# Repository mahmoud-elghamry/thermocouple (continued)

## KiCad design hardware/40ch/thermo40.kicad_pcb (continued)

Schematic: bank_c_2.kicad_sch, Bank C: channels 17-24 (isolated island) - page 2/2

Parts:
C361, C371, C381: 10n C0G; C_0805_2012Metric; MPN GRM2195C1H103JA01D; LCSC C97905
C362, C363, C372, C373, C382, C383: 1n C0G; C_0805_2012Metric; MPN CL21C102JBCNNNC; LCSC C1791
C389, C390, C391, C392, C393, C394, C396, C398, C399: 100n; C_0805_2012Metric; MPN CC0805KRX7R9BB104; LCSC C49678
C395, C397: 1u; C_0805_2012Metric; MPN CL21B105KBFNNNE; LCSC C28323
D361, D362, D371, D372, D381, D382: BAV199; SOT-23; MPN BAV199,215; LCSC C40919
R361, R362, R371, R372, R381, R382: 2.2k; R_0805_2012Metric; MPN 0805W8F2201T5E; LCSC C17520
R363, R364, R373, R374, R383, R384: 1k; R_0805_2012Metric; MPN 0805W8F1001T5E; LCSC C17513
R365, R375, R385: 20M 1%; R_1206_3216Metric; MPN FRG1206F2005TS; LCSC C3000606
U301: AD7124-8BCPZ; LFCSP-32-1EP_5x5mm_P0.5mm_EP3.6x3.6mm; MPN AD7124-8BCPZ; LCSC C97314
U302, U303: TMP126DCKR; SOT-363_SC-70-6; MPN TMP126DCKR; LCSC C5219998

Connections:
+3V3_ISO: C390.1, C394.1, C395.1, C396.1, C397.1, C399.1, D361.2 (K), D362.2 (K), D371.2 (K), D372.2 (K), D381.2 (K), D382.2 (K), U301.2 (IOVDD), U301.26 (AVDD), U301.27 (SYNC), U302.6 (VDD), U303.6 (VDD); also elsewhere on the board
/BANK_C_2/REFOUT_C: C391.1, U301.22 (REFOUT)
/BANK_C_2/REGCAPA_C: C392.1, U301.24 (REGCAPA)
/BANK_C_2/REGCAPD_C: C393.1, U301.1 (REGCAPD)
/BANK_C_2/TC22_NA: C361.2, C363.1, R364.2, U301.17 (AIN11)
/BANK_C_2/TC22_NC: D362.3 (common), R362.2, R364.1
/BANK_C_2/TC22_PA: C361.1, C362.1, R363.2, U301.16 (AIN10)
/BANK_C_2/TC22_PC: D361.3 (common), R361.2, R363.1
/BANK_C_2/TC23_NA: C371.2, C373.1, R374.2, U301.19 (AIN13)
/BANK_C_2/TC23_NC: D372.3 (common), R372.2, R374.1
/BANK_C_2/TC23_PA: C371.1, C372.1, R373.2, U301.18 (AIN12)
/BANK_C_2/TC23_PC: D371.3 (common), R371.2, R373.1
/BANK_C_2/TC24_NA: C381.2, C383.1, R384.2, U301.21 (AIN15)
/BANK_C_2/TC24_NC: D382.3 (common), R382.2, R384.1
/BANK_C_2/TC24_PA: C381.1, C382.1, R383.2, U301.20 (AIN14)
/BANK_C_2/TC24_PC: D381.3 (common), R381.2, R383.1
CS_ADC3_ISO: U301.32 (~CS); also elsewhere on the board
CS_CJ5_ISO: U302.1 (~CS); also elsewhere on the board
CS_CJ6_ISO: U303.1 (~CS); also elsewhere on the board
DIN_ISO: U301.29 (DIN); also elsewhere on the board
DOUT_ISO: U301.28 (DOUT/~RDY), U302.3 (SIO), U303.3 (SIO); also elsewhere on the board
GND_ISO: C389.2, C390.2, C391.2, C392.2, C393.2, C394.2, C395.2, C396.2, C397.2, C398.2, C399.2, D361.1 (A), D362.1 (A), D371.1 (A), D372.1 (A), D381.1 (A), D382.1 (A), U301.3 (DGND), U301.13 (REFIN1(-)), U301.23 (AVSS), U301.33 (EP), U302.2 (GND), U302.5 (ALERT), U303.2 (GND), U303.5 (ALERT); also elsewhere on the board
SCLK_ISO: U301.30 (SCLK), U302.4 (SCLK), U303.4 (SCLK); also elsewhere on the board
TC17_NA: U301.5 (AIN1); also elsewhere on the board
TC17_PA: U301.4 (AIN0); also elsewhere on the board
TC18_NA: U301.7 (AIN3); also elsewhere on the board
TC18_PA: U301.6 (AIN2); also elsewhere on the board
TC19_NA: U301.9 (AIN5); also elsewhere on the board
TC19_PA: U301.8 (AIN4); also elsewhere on the board
TC20_NA: U301.11 (AIN7); also elsewhere on the board
TC20_PA: U301.10 (AIN6); also elsewhere on the board
TC21_NA: U301.15 (AIN9); also elsewhere on the board
TC21_PA: U301.14 (AIN8); also elsewhere on the board
TC22+: R361.1; also elsewhere on the board
TC22-: R362.1, R365.1; also elsewhere on the board
TC23+: R371.1; also elsewhere on the board
TC23-: R372.1, R375.1; also elsewhere on the board
TC24+: R381.1; also elsewhere on the board
TC24-: R382.1, R385.1; also elsewhere on the board
VREF_EXT: C398.1, U301.12 (REFIN1(+)); also elsewhere on the board
V_BIAS: C362.2, C363.2, C372.2, C373.2, C382.2, C383.2, C389.1, R365.2, R375.2, R385.2; also elsewhere on the board

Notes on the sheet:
Channel 22: limiter, clamp, filter, bias
Channel 23: limiter, clamp, filter, bias
Channel 24: limiter, clamp, filter, bias
AD7124-8 #3 and its decoupling
Cold-junction sensors (one per 4-channel header)

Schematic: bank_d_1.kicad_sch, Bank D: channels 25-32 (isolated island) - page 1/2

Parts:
C811, C821, C831, C841, C851: 10n C0G; C_0805_2012Metric; MPN GRM2195C1H103JA01D; LCSC C97905
C812, C813, C822, C823, C832, C833, C842, C843, C852, C853: 1n C0G; C_0805_2012Metric; MPN CL21C102JBCNNNC; LCSC C1791
D811, D812, D821, D822, D831, D832, D841, D842, D851, D852: BAV199; SOT-23; MPN BAV199,215; LCSC C40919
J801: TC CH25-28; PhoenixContact_MC_1,5_8-G-3.81_1x08_P3.81mm_Horizontal; MPN WJ15EDGRC-3.81-8P; LCSC C14235
J802: TC CH29-32; PhoenixContact_MC_1,5_8-G-3.81_1x08_P3.81mm_Horizontal; MPN WJ15EDGRC-3.81-8P; LCSC C14235
R811, R812, R821, R822, R831, R832, R841, R842, R851, R852: 2.2k; R_0805_2012Metric; MPN 0805W8F2201T5E; LCSC C17520
R813, R814, R823, R824, R833, R834, R843, R844, R853, R854: 1k; R_0805_2012Metric; MPN 0805W8F1001T5E; LCSC C17513
R815, R825, R835, R845, R855: 20M 1%; R_1206_3216Metric; MPN FRG1206F2005TS; LCSC C3000606

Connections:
+3V3_ISO: D811.2 (K), D812.2 (K), D821.2 (K), D822.2 (K), D831.2 (K), D832.2 (K), D841.2 (K), D842.2 (K), D851.2 (K), D852.2 (K); also elsewhere on the board
/BANK_D_1/TC25+: J801.1, R811.1
/BANK_D_1/TC25-: J801.2, R812.1, R815.1
/BANK_D_1/TC25_NC: D812.3 (common), R812.2, R814.1
/BANK_D_1/TC25_PC: D811.3 (common), R811.2, R813.1
/BANK_D_1/TC26+: J801.3, R821.1
/BANK_D_1/TC26-: J801.4, R822.1, R825.1
/BANK_D_1/TC26_NC: D822.3 (common), R822.2, R824.1
/BANK_D_1/TC26_PC: D821.3 (common), R821.2, R823.1
/BANK_D_1/TC27+: J801.5, R831.1
/BANK_D_1/TC27-: J801.6, R832.1, R835.1
/BANK_D_1/TC27_NC: D832.3 (common), R832.2, R834.1
/BANK_D_1/TC27_PC: D831.3 (common), R831.2, R833.1
/BANK_D_1/TC28+: J801.7, R841.1
/BANK_D_1/TC28-: J801.8, R842.1, R845.1
/BANK_D_1/TC28_NC: D842.3 (common), R842.2, R844.1
/BANK_D_1/TC28_PC: D841.3 (common), R841.2, R843.1
/BANK_D_1/TC29+: J802.1, R851.1
/BANK_D_1/TC29-: J802.2, R852.1, R855.1
/BANK_D_1/TC29_NC: D852.3 (common), R852.2, R854.1
/BANK_D_1/TC29_PC: D851.3 (common), R851.2, R853.1
GND_ISO: D811.1 (A), D812.1 (A), D821.1 (A), D822.1 (A), D831.1 (A), D832.1 (A), D841.1 (A), D842.1 (A), D851.1 (A), D852.1 (A); also elsewhere on the board
TC25_NA: C811.2, C813.1, R814.2; also elsewhere on the board
TC25_PA: C811.1, C812.1, R813.2; also elsewhere on the board
TC26_NA: C821.2, C823.1, R824.2; also elsewhere on the board
TC26_PA: C821.1, C822.1, R823.2; also elsewhere on the board
TC27_NA: C831.2, C833.1, R834.2; also elsewhere on the board
TC27_PA: C831.1, C832.1, R833.2; also elsewhere on the board
TC28_NA: C841.2, C843.1, R844.2; also elsewhere on the board
TC28_PA: C841.1, C842.1, R843.2; also elsewhere on the board
TC29_NA: C851.2, C853.1, R854.2; also elsewhere on the board
TC29_PA: C851.1, C852.1, R853.2; also elsewhere on the board
TC30+: J802.3; also elsewhere on the board
TC30-: J802.4; also elsewhere on the board
TC31+: J802.5; also elsewhere on the board
TC31-: J802.6; also elsewhere on the board
TC32+: J802.7; also elsewhere on the board
TC32-: J802.8; also elsewhere on the board
V_BIAS: C812.2, C813.2, C822.2, C823.2, C832.2, C833.2, C842.2, C843.2, C852.2, C853.2, R815.2, R825.2, R835.2, R845.2, R855.2; also elsewhere on the board

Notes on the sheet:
Thermocouple terminals (TC+ / TC- per channel; shield goes to the panel-entry bar)
Channel 25: limiter, clamp, filter, bias
Channel 26: limiter, clamp, filter, bias
Channel 27: limiter, clamp, filter, bias
Channel 28: limiter, clamp, filter, bias
Channel 29: limiter, clamp, filter, bias

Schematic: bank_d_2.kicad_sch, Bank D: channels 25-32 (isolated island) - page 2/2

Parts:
C861, C871, C881: 10n C0G; C_0805_2012Metric; MPN GRM2195C1H103JA01D; LCSC C97905
C862, C863, C872, C873, C882, C883: 1n C0G; C_0805_2012Metric; MPN CL21C102JBCNNNC; LCSC C1791
C889, C890, C891, C892, C893, C894, C896, C898, C899: 100n; C_0805_2012Metric; MPN CC0805KRX7R9BB104; LCSC C49678
C895, C897: 1u; C_0805_2012Metric; MPN CL21B105KBFNNNE; LCSC C28323
D861, D862, D871, D872, D881, D882: BAV199; SOT-23; MPN BAV199,215; LCSC C40919
R861, R862, R871, R872, R881, R882: 2.2k; R_0805_2012Metric; MPN 0805W8F2201T5E; LCSC C17520
R863, R864, R873, R874, R883, R884: 1k; R_0805_2012Metric; MPN 0805W8F1001T5E; LCSC C17513
R865, R875, R885: 20M 1%; R_1206_3216Metric; MPN FRG1206F2005TS; LCSC C3000606
U801: AD7124-8BCPZ; LFCSP-32-1EP_5x5mm_P0.5mm_EP3.6x3.6mm; MPN AD7124-8BCPZ; LCSC C97314
U802, U803: TMP126DCKR; SOT-363_SC-70-6; MPN TMP126DCKR; LCSC C5219998

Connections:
+3V3_ISO: C890.1, C894.1, C895.1, C896.1, C897.1, C899.1, D861.2 (K), D862.2 (K), D871.2 (K), D872.2 (K), D881.2 (K), D882.2 (K), U801.2 (IOVDD), U801.26 (AVDD), U801.27 (SYNC), U802.6 (VDD), U803.6 (VDD); also elsewhere on the board
/BANK_D_2/REFOUT_D: C891.1, U801.22 (REFOUT)
/BANK_D_2/REGCAPA_D: C892.1, U801.24 (REGCAPA)
/BANK_D_2/REGCAPD_D: C893.1, U801.1 (REGCAPD)
/BANK_D_2/TC30_NA: C861.2, C863.1, R864.2, U801.17 (AIN11)
/BANK_D_2/TC30_NC: D862.3 (common), R862.2, R864.1
/BANK_D_2/TC30_PA: C861.1, C862.1, R863.2, U801.16 (AIN10)
/BANK_D_2/TC30_PC: D861.3 (common), R861.2, R863.1
/BANK_D_2/TC31_NA: C871.2, C873.1, R874.2, U801.19 (AIN13)
/BANK_D_2/TC31_NC: D872.3 (common), R872.2, R874.1
/BANK_D_2/TC31_PA: C871.1, C872.1, R873.2, U801.18 (AIN12)
/BANK_D_2/TC31_PC: D871.3 (common), R871.2, R873.1
/BANK_D_2/TC32_NA: C881.2, C883.1, R884.2, U801.21 (AIN15)
/BANK_D_2/TC32_NC: D882.3 (common), R882.2, R884.1
/BANK_D_2/TC32_PA: C881.1, C882.1, R883.2, U801.20 (AIN14)
/BANK_D_2/TC32_PC: D881.3 (common), R881.2, R883.1
CS_ADC4_ISO: U801.32 (~CS); also elsewhere on the board
CS_CJ7_ISO: U802.1 (~CS); also elsewhere on the board
CS_CJ8_ISO: U803.1 (~CS); also elsewhere on the board
DIN_ISO: U801.29 (DIN); also elsewhere on the board
DOUT_ISO: U801.28 (DOUT/~RDY), U802.3 (SIO), U803.3 (SIO); also elsewhere on the board
GND_ISO: C889.2, C890.2, C891.2, C892.2, C893.2, C894.2, C895.2, C896.2, C897.2, C898.2, C899.2, D861.1 (A), D862.1 (A), D871.1 (A), D872.1 (A), D881.1 (A), D882.1 (A), U801.3 (DGND), U801.13 (REFIN1(-)), U801.23 (AVSS), U801.33 (EP), U802.2 (GND), U802.5 (ALERT), U803.2 (GND), U803.5 (ALERT); also elsewhere on the board
SCLK_ISO: U801.30 (SCLK), U802.4 (SCLK), U803.4 (SCLK); also elsewhere on the board
TC25_NA: U801.5 (AIN1); also elsewhere on the board
TC25_PA: U801.4 (AIN0); also elsewhere on the board
TC26_NA: U801.7 (AIN3); also elsewhere on the board
TC26_PA: U801.6 (AIN2); also elsewhere on the board
TC27_NA: U801.9 (AIN5); also elsewhere on the board
TC27_PA: U801.8 (AIN4); also elsewhere on the board
TC28_NA: U801.11 (AIN7); also elsewhere on the board
TC28_PA: U801.10 (AIN6); also elsewhere on the board
TC29_NA: U801.15 (AIN9); also elsewhere on the board
TC29_PA: U801.14 (AIN8); also elsewhere on the board
TC30+: R861.1; also elsewhere on the board
TC30-: R862.1, R865.1; also elsewhere on the board
TC31+: R871.1; also elsewhere on the board
TC31-: R872.1, R875.1; also elsewhere on the board
TC32+: R881.1; also elsewhere on the board
TC32-: R882.1, R885.1; also elsewhere on the board
VREF_EXT: C898.1, U801.12 (REFIN1(+)); also elsewhere on the board
V_BIAS: C862.2, C863.2, C872.2, C873.2, C882.2, C883.2, C889.1, R865.2, R875.2, R885.2; also elsewhere on the board

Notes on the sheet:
Channel 30: limiter, clamp, filter, bias
Channel 31: limiter, clamp, filter, bias
Channel 32: limiter, clamp, filter, bias
AD7124-8 #4 and its decoupling
Cold-junction sensors (one per 4-channel header)

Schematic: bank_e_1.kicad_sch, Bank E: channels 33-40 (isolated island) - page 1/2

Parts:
C911, C921, C931, C941, C951: 10n C0G; C_0805_2012Metric; MPN GRM2195C1H103JA01D; LCSC C97905
C912, C913, C922, C923, C932, C933, C942, C943, C952, C953: 1n C0G; C_0805_2012Metric; MPN CL21C102JBCNNNC; LCSC C1791
D911, D912, D921, D922, D931, D932, D941, D942, D951, D952: BAV199; SOT-23; MPN BAV199,215; LCSC C40919
J901: TC CH33-36; PhoenixContact_MC_1,5_8-G-3.81_1x08_P3.81mm_Horizontal; MPN WJ15EDGRC-3.81-8P; LCSC C14235
J902: TC CH37-40; PhoenixContact_MC_1,5_8-G-3.81_1x08_P3.81mm_Horizontal; MPN WJ15EDGRC-3.81-8P; LCSC C14235
R911, R912, R921, R922, R931, R932, R941, R942, R951, R952: 2.2k; R_0805_2012Metric; MPN 0805W8F2201T5E; LCSC C17520
R913, R914, R923, R924, R933, R934, R943, R944, R953, R954: 1k; R_0805_2012Metric; MPN 0805W8F1001T5E; LCSC C17513
R915, R925, R935, R945, R955: 20M 1%; R_1206_3216Metric; MPN FRG1206F2005TS; LCSC C3000606

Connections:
+3V3_ISO: D911.2 (K), D912.2 (K), D921.2 (K), D922.2 (K), D931.2 (K), D932.2 (K), D941.2 (K), D942.2 (K), D951.2 (K), D952.2 (K); also elsewhere on the board
/BANK_E_1/TC33+: J901.1, R911.1
/BANK_E_1/TC33-: J901.2, R912.1, R915.1
/BANK_E_1/TC33_NC: D912.3 (common), R912.2, R914.1
/BANK_E_1/TC33_PC: D911.3 (common), R911.2, R913.1
/BANK_E_1/TC34+: J901.3, R921.1
/BANK_E_1/TC34-: J901.4, R922.1, R925.1
/BANK_E_1/TC34_NC: D922.3 (common), R922.2, R924.1
/BANK_E_1/TC34_PC: D921.3 (common), R921.2, R923.1
/BANK_E_1/TC35+: J901.5, R931.1
/BANK_E_1/TC35-: J901.6, R932.1, R935.1
/BANK_E_1/TC35_NC: D932.3 (common), R932.2, R934.1
/BANK_E_1/TC35_PC: D931.3 (common), R931.2, R933.1
/BANK_E_1/TC36+: J901.7, R941.1
/BANK_E_1/TC36-: J901.8, R942.1, R945.1
/BANK_E_1/TC36_NC: D942.3 (common), R942.2, R944.1
/BANK_E_1/TC36_PC: D941.3 (common), R941.2, R943.1
/BANK_E_1/TC37+: J902.1, R951.1
/BANK_E_1/TC37-: J902.2, R952.1, R955.1
/BANK_E_1/TC37_NC: D952.3 (common), R952.2, R954.1
/BANK_E_1/TC37_PC: D951.3 (common), R951.2, R953.1
GND_ISO: D911.1 (A), D912.1 (A), D921.1 (A), D922.1 (A), D931.1 (A), D932.1 (A), D941.1 (A), D942.1 (A), D951.1 (A), D952.1 (A); also elsewhere on the board
TC33_NA: C911.2, C913.1, R914.2; also elsewhere on the board
TC33_PA: C911.1, C912.1, R913.2; also elsewhere on the board
TC34_NA: C921.2, C923.1, R924.2; also elsewhere on the board
TC34_PA: C921.1, C922.1, R923.2; also elsewhere on the board
TC35_NA: C931.2, C933.1, R934.2; also elsewhere on the board
TC35_PA: C931.1, C932.1, R933.2; also elsewhere on the board
TC36_NA: C941.2, C943.1, R944.2; also elsewhere on the board
TC36_PA: C941.1, C942.1, R943.2; also elsewhere on the board
TC37_NA: C951.2, C953.1, R954.2; also elsewhere on the board
TC37_PA: C951.1, C952.1, R953.2; also elsewhere on the board
TC38+: J902.3; also elsewhere on the board
TC38-: J902.4; also elsewhere on the board
TC39+: J902.5; also elsewhere on the board
TC39-: J902.6; also elsewhere on the board
TC40+: J902.7; also elsewhere on the board
TC40-: J902.8; also elsewhere on the board
V_BIAS: C912.2, C913.2, C922.2, C923.2, C932.2, C933.2, C942.2, C943.2, C952.2, C953.2, R915.2, R925.2, R935.2, R945.2, R955.2; also elsewhere on the board

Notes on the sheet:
Thermocouple terminals (TC+ / TC- per channel; shield goes to the panel-entry bar)
Channel 33: limiter, clamp, filter, bias
Channel 34: limiter, clamp, filter, bias
Channel 35: limiter, clamp, filter, bias
Channel 36: limiter, clamp, filter, bias
Channel 37: limiter, clamp, filter, bias

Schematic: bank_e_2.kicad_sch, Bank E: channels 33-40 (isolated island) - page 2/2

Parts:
C961, C971, C981: 10n C0G; C_0805_2012Metric; MPN GRM2195C1H103JA01D; LCSC C97905
C962, C963, C972, C973, C982, C983: 1n C0G; C_0805_2012Metric; MPN CL21C102JBCNNNC; LCSC C1791
C989, C990, C991, C992, C993, C994, C996, C998, C999: 100n; C_0805_2012Metric; MPN CC0805KRX7R9BB104; LCSC C49678
C995, C997: 1u; C_0805_2012Metric; MPN CL21B105KBFNNNE; LCSC C28323
D961, D962, D971, D972, D981, D982: BAV199; SOT-23; MPN BAV199,215; LCSC C40919
R961, R962, R971, R972, R981, R982: 2.2k; R_0805_2012Metric; MPN 0805W8F2201T5E; LCSC C17520
R963, R964, R973, R974, R983, R984: 1k; R_0805_2012Metric; MPN 0805W8F1001T5E; LCSC C17513
R965, R975, R985: 20M 1%; R_1206_3216Metric; MPN FRG1206F2005TS; LCSC C3000606
U901: AD7124-8BCPZ; LFCSP-32-1EP_5x5mm_P0.5mm_EP3.6x3.6mm; MPN AD7124-8BCPZ; LCSC C97314
U902, U903: TMP126DCKR; SOT-363_SC-70-6; MPN TMP126DCKR; LCSC C5219998

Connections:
+3V3_ISO: C990.1, C994.1, C995.1, C996.1, C997.1, C999.1, D961.2 (K), D962.2 (K), D971.2 (K), D972.2 (K), D981.2 (K), D982.2 (K), U901.2 (IOVDD), U901.26 (AVDD), U901.27 (SYNC), U902.6 (VDD), U903.6 (VDD); also elsewhere on the board
/BANK_E_2/REFOUT_E: C991.1, U901.22 (REFOUT)
/BANK_E_2/REGCAPA_E: C992.1, U901.24 (REGCAPA)
/BANK_E_2/REGCAPD_E: C993.1, U901.1 (REGCAPD)
/BANK_E_2/TC38_NA: C961.2, C963.1, R964.2, U901.17 (AIN11)
/BANK_E_2/TC38_NC: D962.3 (common), R962.2, R964.1
/BANK_E_2/TC38_PA: C961.1, C962.1, R963.2, U901.16 (AIN10)
/BANK_E_2/TC38_PC: D961.3 (common), R961.2, R963.1
/BANK_E_2/TC39_NA: C971.2, C973.1, R974.2, U901.19 (AIN13)
/BANK_E_2/TC39_NC: D972.3 (common), R972.2, R974.1
/BANK_E_2/TC39_PA: C971.1, C972.1, R973.2, U901.18 (AIN12)
/BANK_E_2/TC39_PC: D971.3 (common), R971.2, R973.1
/BANK_E_2/TC40_NA: C981.2, C983.1, R984.2, U901.21 (AIN15)
/BANK_E_2/TC40_NC: D982.3 (common), R982.2, R984.1
/BANK_E_2/TC40_PA: C981.1, C982.1, R983.2, U901.20 (AIN14)
/BANK_E_2/TC40_PC: D981.3 (common), R981.2, R983.1
CS_ADC5_ISO: U901.32 (~CS); also elsewhere on the board
CS_CJ9_ISO: U902.1 (~CS); also elsewhere on the board
CS_CJ10_ISO: U903.1 (~CS); also elsewhere on the board
DIN_ISO: U901.29 (DIN); also elsewhere on the board
DOUT_ISO: U901.28 (DOUT/~RDY), U902.3 (SIO), U903.3 (SIO); also elsewhere on the board
GND_ISO: C989.2, C990.2, C991.2, C992.2, C993.2, C994.2, C995.2, C996.2, C997.2, C998.2, C999.2, D961.1 (A), D962.1 (A), D971.1 (A), D972.1 (A), D981.1 (A), D982.1 (A), U901.3 (DGND), U901.13 (REFIN1(-)), U901.23 (AVSS), U901.33 (EP), U902.2 (GND), U902.5 (ALERT), U903.2 (GND), U903.5 (ALERT); also elsewhere on the board
SCLK_ISO: U901.30 (SCLK), U902.4 (SCLK), U903.4 (SCLK); also elsewhere on the board
TC33_NA: U901.5 (AIN1); also elsewhere on the board
TC33_PA: U901.4 (AIN0); also elsewhere on the board
TC34_NA: U901.7 (AIN3); also elsewhere on the board
TC34_PA: U901.6 (AIN2); also elsewhere on the board
TC35_NA: U901.9 (AIN5); also elsewhere on the board
TC35_PA: U901.8 (AIN4); also elsewhere on the board
TC36_NA: U901.11 (AIN7); also elsewhere on the board
TC36_PA: U901.10 (AIN6); also elsewhere on the board
TC37_NA: U901.15 (AIN9); also elsewhere on the board
TC37_PA: U901.14 (AIN8); also elsewhere on the board
TC38+: R961.1; also elsewhere on the board
TC38-: R962.1, R965.1; also elsewhere on the board
TC39+: R971.1; also elsewhere on the board
TC39-: R972.1, R975.1; also elsewhere on the board
TC40+: R981.1; also elsewhere on the board
TC40-: R982.1, R985.1; also elsewhere on the board
VREF_EXT: C998.1, U901.12 (REFIN1(+)); also elsewhere on the board
V_BIAS: C962.2, C963.2, C972.2, C973.2, C982.2, C983.2, C989.1, R965.2, R975.2, R985.2; also elsewhere on the board

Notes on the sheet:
Channel 38: limiter, clamp, filter, bias
Channel 39: limiter, clamp, filter, bias
Channel 40: limiter, clamp, filter, bias
AD7124-8 #5 and its decoupling
Cold-junction sensors (one per 4-channel header)

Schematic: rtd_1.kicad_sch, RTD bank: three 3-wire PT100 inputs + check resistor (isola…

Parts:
C1011, C1021, C1031, C1041: 10n C0G; C_0805_2012Metric; MPN GRM2195C1H103JA01D; LCSC C97905
C1012, C1013, C1022, C1023, C1032, C1033, C1042, C1043: 1n C0G; C_0805_2012Metric; MPN CL21C102JBCNNNC; LCSC C1791
D1011, D1012, D1013, D1014, D1021, D1022, D1023, D1024, D1031, D1032, D1033, D1034, D1041, D1042, D1043, D1044: BAV199; SOT-23; MPN BAV199,215; LCSC C40919
J1001: PT100 1-2 (A B C); PhoenixContact_MC_1,5_6-G-3.81_1x06_P3.81mm_Horizontal; MPN WJ15EDGRC-3.81-06P; LCSC C7246
J1002: PT100 3 (A B C); PhoenixContact_MC_1,5_3-G-3.81_1x03_P3.81mm_Horizontal; MPN WJ15EDGRC-3.81-03P; LCSC C8406
R1011, R1013, R1019, R1021, R1023, R1029, R1031, R1033, R1039, R1041, R1043, R1049: 1k 1W; R_2512_6332Metric; MPN 25121WF1001T4E; LCSC C54315
R1012, R1014, R1022, R1024, R1032, R1034, R1042, R1044: 100R; R_0805_2012Metric; MPN 0805W8F1000T5E; LCSC C17408
R1015, R1017, R1025, R1027, R1035, R1037, R1045, R1047: 2.2k; R_1206_3216Metric; MPN 1206W4F2201T5E; LCSC C17948
R1016, R1018, R1026, R1028, R1036, R1038, R1046, R1048: 1k; R_0805_2012Metric; MPN 0805W8F1001T5E; LCSC C17513
R1095: 150R 0.1%; R_0805_2012Metric; MPN RT0805BRD07150RL; LCSC C513734

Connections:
+3V3_ISO: D1011.2 (K), D1012.2 (K), D1013.2 (K), D1014.2 (K), D1021.2 (K), D1022.2 (K), D1023.2 (K), D1024.2 (K), D1031.2 (K), D1032.2 (K), D1033.2 (K), D1034.2 (K), D1041.2 (K), D1042.2 (K), D1043.2 (K), D1044.2 (K); also elsewhere on the board
/RTD_1/CHK_A: R1041.1, R1045.1, R1095.1
/RTD_1/CHK_BC: R1043.1, R1047.1, R1049.1, R1095.2
/RTD_1/RTD1_A: J1001.1, R1011.1, R1015.1
/RTD_1/RTD1_B: J1001.2, R1013.1, R1017.1
/RTD_1/RTD1_C: J1001.3, R1019.1
/RTD_1/RTD1_SAC: D1013.3 (common), R1015.2, R1016.1
/RTD_1/RTD1_SBC: D1014.3 (common), R1017.2, R1018.1
/RTD_1/RTD1_XA: D1011.3 (common), R1011.2, R1012.1
/RTD_1/RTD1_XB: D1012.3 (common), R1013.2, R1014.1
/RTD_1/RTD2_A: J1001.4, R1021.1, R1025.1
/RTD_1/RTD2_B: J1001.5, R1023.1, R1027.1
/RTD_1/RTD2_C: J1001.6, R1029.1
/RTD_1/RTD2_SAC: D1023.3 (common), R1025.2, R1026.1
/RTD_1/RTD2_SBC: D1024.3 (common), R1027.2, R1028.1
/RTD_1/RTD2_XA: D1021.3 (common), R1021.2, R1022.1
/RTD_1/RTD2_XB: D1022.3 (common), R1023.2, R1024.1
/RTD_1/RTD3_A: J1002.1, R1031.1, R1035.1
/RTD_1/RTD3_B: J1002.2, R1033.1, R1037.1
/RTD_1/RTD3_C: J1002.3, R1039.1
/RTD_1/RTD3_SAC: D1033.3 (common), R1035.2, R1036.1
/RTD_1/RTD3_SBC: D1034.3 (common), R1037.2, R1038.1
/RTD_1/RTD3_XA: D1031.3 (common), R1031.2, R1032.1
/RTD_1/RTD3_XB: D1032.3 (common), R1033.2, R1034.1
/RTD_1/RTD4_SAC: D1043.3 (common), R1045.2, R1046.1
/RTD_1/RTD4_SBC: D1044.3 (common), R1047.2, R1048.1
/RTD_1/RTD4_XA: D1041.3 (common), R1041.2, R1042.1
/RTD_1/RTD4_XB: D1042.3 (common), R1043.2, R1044.1
GND_ISO: D1011.1 (A), D1012.1 (A), D1013.1 (A), D1014.1 (A), D1021.1 (A), D1022.1 (A), D1023.1 (A), D1024.1 (A), D1031.1 (A), D1032.1 (A), D1033.1 (A), D1034.1 (A), D1041.1 (A), D1042.1 (A), D1043.1 (A), D1044.1 (A); also elsewhere on the board
RTD1_IA: R1012.2; also elsewhere on the board
RTD1_IB: R1014.2; also elsewhere on the board
RTD1_SN: C1011.2, C1013.1, R1018.2; also elsewhere on the board
RTD1_SP: C1011.1, C1012.1, R1016.2; also elsewhere on the board
RTD2_IA: R1022.2; also elsewhere on the board
RTD2_IB: R1024.2; also elsewhere on the board
RTD2_SN: C1021.2, C1023.1, R1028.2; also elsewhere on the board
RTD2_SP: C1021.1, C1022.1, R1026.2; also elsewhere on the board
RTD3_IA: R1032.2; also elsewhere on the board
RTD3_IB: R1034.2; also elsewhere on the board
RTD3_SN: C1031.2, C1033.1, R1038.2; also elsewhere on the board
RTD3_SP: C1031.1, C1032.1, R1036.2; also elsewhere on the board
RTD4_IA: R1042.2; also elsewhere on the board
RTD4_IB: R1044.2; also elsewhere on the board
RTD4_SN: C1041.2, C1043.1, R1048.2; also elsewhere on the board
RTD4_SP: C1041.1, C1042.1, R1046.2; also elsewhere on the board
RTD_RET: C1012.2, C1013.2, C1022.2, C1023.2, C1032.2, C1033.2, C1042.2, C1043.2, R1019.2, R1029.2, R1039.2, R1049.2; also elsewhere on the board

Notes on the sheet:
PT100 terminals: A = single-wire end, B + C = the two wires of the other end
PT100 1: excitation and sense branches, filter, return
PT100 2: excitation and sense branches, filter, return
PT100 3: excitation and sense branches, filter, return
Check channel (0039 P5 (b)): a precision resistor through the same network, read every scan

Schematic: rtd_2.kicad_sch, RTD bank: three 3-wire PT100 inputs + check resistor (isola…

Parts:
C1090, C1091, C1092, C1093, C1094, C1096: 100n; C_0805_2012Metric; MPN CC0805KRX7R9BB104; LCSC C49678
C1095, C1097: 1u; C_0805_2012Metric; MPN CL21B105KBFNNNE; LCSC C28323
D1091: BAV199; SOT-23; MPN BAV199,215; LCSC C40919
R1092: 2.49k 0.1%; R_0805_2012Metric; MPN RT0805BRD072K49L; LCSC C375522
R1093: 330R; R_0805_2012Metric; MPN 0805W8F3300T5E; LCSC C17630
U1001: AD7124-8BCPZ; LFCSP-32-1EP_5x5mm_P0.5mm_EP3.6x3.6mm; MPN AD7124-8BCPZ; LCSC C97314

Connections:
+3V3_ISO: C1094.1, C1095.1, C1096.1, C1097.1, D1091.2 (K), U1001.2 (IOVDD), U1001.26 (AVDD), U1001.27 (SYNC); also elsewhere on the board
/RTD_2/REFOUT_R: C1091.1, U1001.22 (REFOUT)
/RTD_2/REGCAPA_R: C1092.1, U1001.24 (REGCAPA)
/RTD_2/REGCAPD_R: C1093.1, U1001.1 (REGCAPD)
/RTD_2/RTD_REFN: C1090.2, R1092.2, R1093.1, U1001.13 (REFIN1(-))
CS_RTD_ISO: U1001.32 (~CS); also elsewhere on the board
DIN_ISO: U1001.29 (DIN); also elsewhere on the board
DOUT_ISO: U1001.28 (DOUT/~RDY); also elsewhere on the board
GND_ISO: C1091.2, C1092.2, C1093.2, C1094.2, C1095.2, C1096.2, C1097.2, D1091.1 (A), R1093.2, U1001.3 (DGND), U1001.23 (AVSS), U1001.33 (EP); also elsewhere on the board
RTD1_IA: U1001.4 (AIN0); also elsewhere on the board
RTD1_IB: U1001.5 (AIN1); also elsewhere on the board
RTD1_SN: U1001.7 (AIN3); also elsewhere on the board
RTD1_SP: U1001.6 (AIN2); also elsewhere on the board
RTD2_IA: U1001.8 (AIN4); also elsewhere on the board
RTD2_IB: U1001.9 (AIN5); also elsewhere on the board
RTD2_SN: U1001.11 (AIN7); also elsewhere on the board
RTD2_SP: U1001.10 (AIN6); also elsewhere on the board
RTD3_IA: U1001.14 (AIN8); also elsewhere on the board
RTD3_IB: U1001.15 (AIN9); also elsewhere on the board
RTD3_SN: U1001.17 (AIN11); also elsewhere on the board
RTD3_SP: U1001.16 (AIN10); also elsewhere on the board
RTD4_IA: U1001.18 (AIN12); also elsewhere on the board
RTD4_IB: U1001.19 (AIN13); also elsewhere on the board
RTD4_SN: U1001.21 (AIN15); also elsewhere on the board
RTD4_SP: U1001.20 (AIN14); also elsewhere on the board
RTD_RET: C1090.1, D1091.3 (common), R1092.1, U1001.12 (REFIN1(+)); also elsewhere on the board
SCLK_ISO: U1001.30 (SCLK); also elsewhere on the board

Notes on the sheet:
AD7124-8 (RTD), reference resistor and decoupling

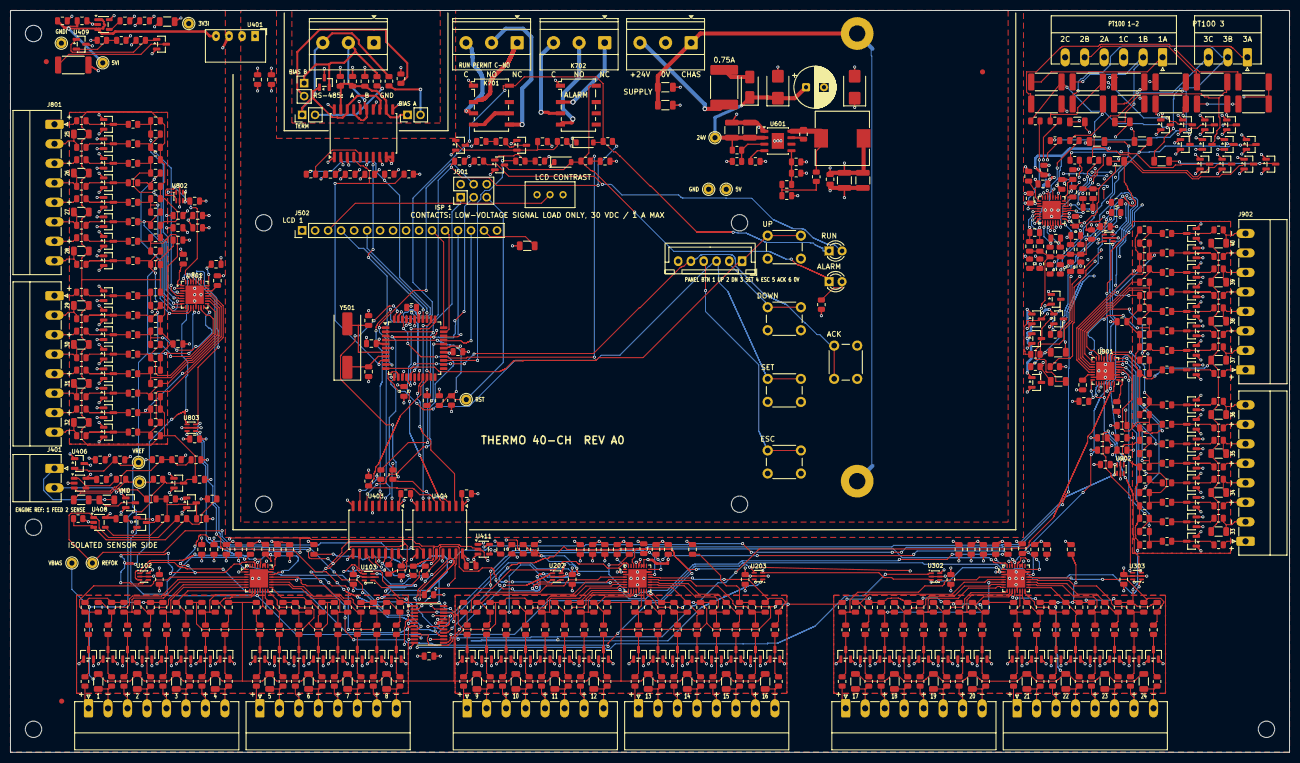
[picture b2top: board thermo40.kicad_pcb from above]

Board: 4 copper layers, 250.0 x 145.0 mm, 731 parts (0 on the bottom side), 423 nets.

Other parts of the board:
FID1, FID2, FID3: Fiducial_1mm_Mask2mm

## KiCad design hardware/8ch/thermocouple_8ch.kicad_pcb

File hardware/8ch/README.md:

# 8-channel thermocouple protection board — engineering prototype

**Status: not released for fabrication.** See “Where this actually stands”
below before drawing any conclusion from a clean check report.

This directory is a self-contained KiCad 10 project. It does not share files
with, and must not be confused with, the single-channel board in `hardware/single-channel/`.

---

## What the board is

| | |
|---|---|
| Size / stack-up | 250 × 140 mm, 4 layers |
| Measurement | 8 × MAX31856, one per K-type input, on a shared isolated island |
| Controller | ATmega32A-PU in a DIP-40 socket, internal RC oscillator, 5 V |
| Local HMI | 16×2 HD44780 in 4-bit mode, five buttons, contrast pot |
| Output | Energised-to-run SPDT dry contact (G5LE-1 24 V) via a BSS131 (240 V) low-side switch, REV A2 (`0022`) |
| Comms | Isolated half-duplex RS-485 (ADM2587E) with jumper-selected termination and bias |
| Supply | 24 VDC in → PTC + series Schottky + TVS → TSR 1-2450 → 5 V |
| Sensor supply | IA0505S isolated DC-DC → LP2985-3.3 → +3V3_SENS |

### Layer stack-up

```
F.Cu    signal + ground pour
In1.Cu  ground planes   GND_SENS | GND_CTRL | GND_RS485
In2.Cu  supply planes   +3V3_SENS | +5V_CTRL | +5V_RS485
B.Cu    signal + ground pour + chassis/PE ring
```

No signal is routed on In1 or In2. Every outer-layer track therefore has an
uninterrupted return directly beneath it, and the In1/In2 pair provides the
interplane capacitance that does most of the high-frequency decoupling for the
microvolt front end.

### Three copper islands

```
      x=6           x=145  x=151.5                  x=208 x=214     x=244
   +-----------------+ gap +-------------------------+ gap +---------+
   |  SENSOR ISLAND  |     |  CONTROL ISLAND         |     |         |  y=6
   |  8 × MAX31856   |     |  ATmega32A, LCD,        |     |(control)|
   |  GND_SENS       |     |  relay, 24 V input      |     |         |  y=97
   |  +3V3_SENS      |     |                   ------+-----+---------+
   |                 |     |                   | gap band            |  y=99
   |                 |     |                   |   RS-485 ISLAND     |
   +-----------------+     +-------------------+   GND_RS485         |  y=134
```

Signals cross a barrier only through U10/U11 (ISO7760 / ISO7761) and U15
(ADM2587E). The gap bands are emitted as KiCad rule areas, so the autorouter
cannot bridge them and a reviewer can see the intent on the board.

A fourth net, `CHASSIS_SHIELD`, is the cable-shield / protective-earth
reference. It is a B.Cu loop 3 mm inside the board edge, bonded to the four
plated M3 mounting holes, to J1.3, J4.4 and the eight thermocouple shield
screws — deliberately isolated from all three signal grounds so a shield
current cannot become a measurement ground loop.

---

## Files

| File | Role |
|---|---|
| `thermocouple_8ch.kicad_sch` | schematic root (A4 index) — the structural source of truth, with its sheets: |
| `power` / `mcu` / `isolation` / `relay_rs485.kicad_sch` | one A4 sheet per function (`docs/decisions/0021`) |
| `channel.kicad_sch` | the thermocouple channel, drawn once, used by TC1-TC8 (`0019`) |
| `thermocouple_8ch.kicad_pcb` | board |
| `thermocouple_8ch.kicad_pro` | project, **including the net classes** |
| `thermocouple_8ch.kicad_dru` | custom clearance rules (isolation, relay, chassis) |
| `sch_layout/build.py` | builds the schematic (base `05d6abd` + `sch_layout/`), with its own ERC and netlist gate |
| `kit_list.py` | the technician's through-hole kit list |
| `apply_rules.py` | writes net classes and `.kicad_dru` into the project |
| `board/` | the generator, split by responsibility - see `board/__init__.py` |
| `generate_board.py` | command-line entry point for `board/` |
| `route.py` | DSN → Freerouting → SES, then pours, stitching and finishing |
| `close_gaps.py` | joins anything DRC still reports as unconnected |
| `check_board.py` | structural checks DRC cannot make (islands, barriers, decoupling, cold junction, filter symmetry) |
| `run_all.ps1` | snapshot validation by default; explicit regeneration after owner authorization |
| `validate.ps1` / `check_commands.ps1` | fresh copy, source hashes, checked native exits and report gates |
| `test_gates.ps1` | fault injection for native-command and report failures |

Design rules live in the **project**, not in the scripts. Anyone opening
`thermocouple_8ch.kicad_pro` in KiCad sees the same track widths, via sizes and
clearances the generator used.

---

## Validating and rebuilding

```powershell
pwsh -File hardware\8ch\run_all.ps1
```

The default validates a fresh snapshot under `production/` without changing the
source hardware, including zone refill on the copy before DRC. Errors stop the
pipeline; warnings remain visible. Full regeneration requires `-Regenerate`; the owner lifted the REV A0 freeze
(`docs/decisions/0014`), so run `board_provenance.py --check` first. The commands
below are the regeneration sequence:

```bash
python sch_layout/build.py --in-place
kicad-cli sch erc --output erc-report.rpt --severity-error --severity-warning thermocouple_8ch.kicad_sch
kicad-cli sch export netlist --output thermocouple_8ch.net thermocouple_8ch.kicad_sch
python apply_rules.py
kicad-tool pcb sync thermocouple_8ch.kicad_pcb thermocouple_8ch.kicad_sch
"C:\Program Files\KiCad\10.0\bin\python.exe" generate_board.py
"C:\Program Files\KiCad\10.0\bin\python.exe" route.py --passes 40 --threads 1
"C:\Program Files\KiCad\10.0\bin\python.exe" check_board.py
kicad-cli pcb drc --output drc-report.rpt --severity-error --severity-warning --schematic-parity thermocouple_8ch.kicad_pcb
```

`generate_board.py` and `route.py` need KiCad 10's bundled Python (`pcbnew`).
Re-running regeneration discards the existing routing. Snapshot validation
checks the current saved board without relying on regeneration reproducibility.

### External tools

Routing needs **Freerouting 2.4.x** and a **Java 25** runtime. Neither is in
this repository. Defaults are `%LOCALAPPDATA%\kicad-tools\freerouting.jar` and
`%LOCALAPPDATA%\kicad-tools\jre25\*\bin\java.exe`; override with
`FREEROUTING_JAR` and `FREEROUTING_JAVA`. Freerouting 2.4.1 is compiled to
class-file version 69, so a Java 21 runtime will not load it.

---

## Check results

Read `erc-report.rpt` and `drc-report.rpt`; these numbers come from them.

| Check | Before | Now |
|---|---|---|
| clearance | 304 | **0** |
| shorting items | 19 | **0** |
| tracks crossing | 22 | **0** |
| dangling vias | 7 | 1 (warning) |
| hole clearance / hole-to-hole | 6 / 5 | **0 / 0** |
| zones intersecting | 2 | **0** |
| starved thermals | 2 | **0** |
| solder-mask bridges | 2 | **0** |
| footprint/symbol field mismatch | 146 | **0** |
| silkscreen overlap / over pad | 10 / 3 | 6 / 2 (warnings) |
| **unconnected items** | 46 | **0** |
| **schematic ↔ PCB parity** | — | **0** |
| ERC errors | 7 | **0** |
| ERC warnings | 189 | 171 (all `endpoint_off_grid`) |

**Zero errors.** The nine remaining violations are warnings: six silkscreen
overlaps, two pieces of silkscreen over a pad, and one dangling via.

`check_board.py` passes all six structural checks that DRC cannot make - island
membership, isolation barrier, decoupling proximity, cold-junction distance,
input-filter symmetry and routing completeness. Zero courtyard overlaps, zero
parts off the board edge, all 167 footprints carry a courtyard.

### Fabrication output

Generated into `production/8ch/` (not committed - regenerate it):

```bash
kicad-cli pcb export gerbers --output ../../production/8ch/     --layers F.Cu,In1.Cu,In2.Cu,B.Cu,F.Paste,B.Paste,F.Silkscreen,B.Silkscreen,F.Mask,B.Mask,Edge.Cuts     --subtract-soldermask thermocouple_8ch.kicad_pcb
kicad-cli pcb export drill --output ../../production/8ch/ --format excellon     --drill-origin absolute --excellon-units mm --generate-map --map-format gerberx2 thermocouple_8ch.kicad_pcb
kicad-cli pcb export pos --output ../../production/8ch/thermocouple_8ch-pos.csv     --format csv --units mm --side both thermocouple_8ch.kicad_pcb
kicad-cli pcb export ipcd356 --output ../../production/8ch/thermocouple_8ch.d356 thermocouple_8ch.kicad_pcb
```

Eleven Gerber layers, Excellon drill plus map, the `.gbrjob`, a placement CSV
and an IPC-D-356 netlist for the fab's electrical test.

**Do not hand-edit the board.** `generate_board.py` clears every track, via,
zone and drawing, so anything drawn by hand in KiCad is erased on the next run.
Fixes belong in `board/` or in `route.py`.

---

## Where this actually stands

Nothing here makes this board safe to put on a machine. The following remain
open and none of them can be closed by DRC, ERC, or a 3D render:

- **The shared sensor island is a conditional proof of concept.** It isolates
  the group of eight channels from the controller. It does **not** isolate the
  channels from each other. It is only valid if the eight thermocouple sheaths
  are measured to be at the same potential, on the same equipotential bond.
  That measurement has not been made.
- **MAX31856 is not a galvanic isolator.** It is a better thermocouple
  front end than MAX6675 — filtering, fault detection, input protection — but
  T+/T− are not separated from AGND/DGND. Its presence does not solve a
  grounded tip or a 50 m cable.
- **The isolation rules are functional, not certified.** `.kicad_dru` enforces
  3 mm between islands. That number comes from the tightest part on the board
  (the IA0505S module's own pin pitch), not from a creepage/clearance analysis
  against IEC 61010 at a stated working voltage and pollution degree.
- **The PE ring's spacing is set by connector geometry.** Screw terminals put
  the shield pin 5.00 mm from the adjacent signal pin, which leaves 2.4 mm of
  copper gap. The chassis clearance rule is 1.5 mm for that reason. It is not
  a mains-rated separation.
- **The dry contact is marked LOW-VOLTAGE LOAD ONLY** and its clearances are
  chosen to match that, not a mains rating.
- **No noise, EMC or real-sensor testing has been done.** Cables run about 50 m
  from engine cylinder bodies to a separate panel, with no VFD in the installation.
  Layout symmetry and a plane pair improve the odds;
  they do not substitute for measurement.
- **The unregulated isolated DC-DC needs review.** IA0505S is an unregulated
  ±5 V module. At the ~12 % load this island draws, its output can sit well
  above 5 V. The AP2112K was replaced by LP2985-3.3 with a higher input rating
  (decision 0002), but the converter's real output still needs measurement.
- **DRDY and FAULT are not brought to the MCU.** Both isolators are fully
  allocated (ISO7760: 6/6 forward; ISO7761: 5 forward + 1 reverse for MISO), so
  crossing sixteen more signals needs a second isolator plus fault-OR logic.
  The firmware reads the MAX31856 fault register (0x0F) on every sample. This
  is a deliberate trade-off — see the plan document — not an oversight.
- **Stock and price snapshots in `passives_catalog.json` are not a live
  availability guarantee.** Re-check before ordering.

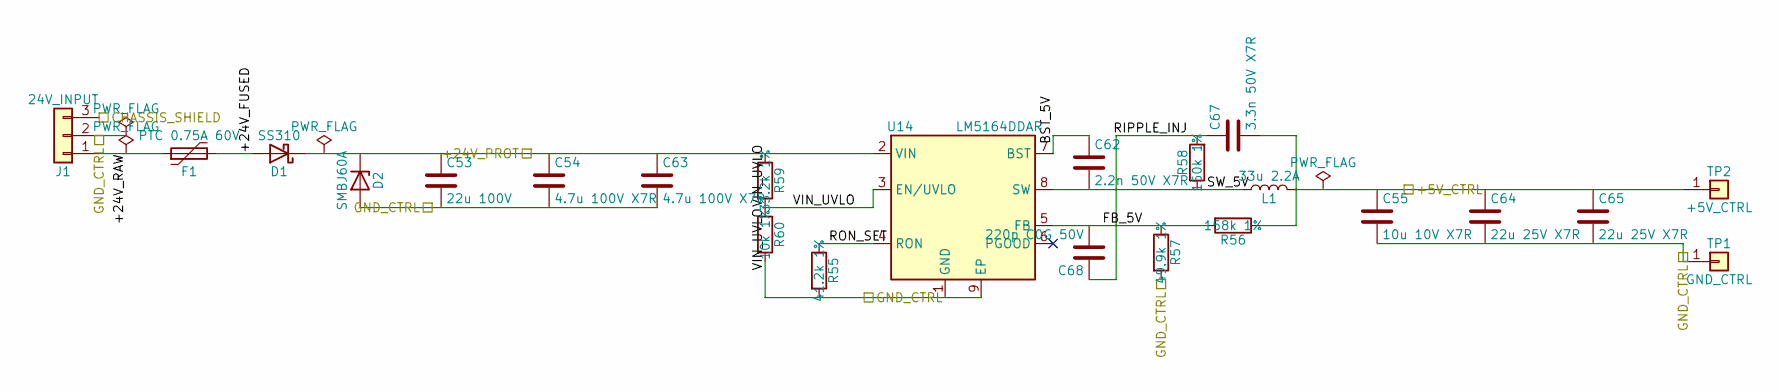
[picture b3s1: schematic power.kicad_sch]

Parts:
C53: 22u 100V; CP_Radial_D8.0mm_P3.50mm; MPN 100YXF22MEFC8X11.5; LCSC C88838
C54, C63: 4.7u 100V X7R; C_1210_3225Metric; MPN FS32X475K101EGG; LCSC C381466
C55: 10u 10V X7R; C_0805_2012Metric; MPN CL21B106KOQNNNE; LCSC C95841
C62: 2.2n 50V X7R; C_0805_2012Metric; MPN CC0805KRX7R9BB222; LCSC C107146
C64, C65: 22u 25V X7R; C_1210_3225Metric; MPN CL32B226KAJNNNE; LCSC C309062
C67: 3.3n 50V X7R; C_0805_2012Metric; MPN 0805B332K500NT; LCSC C1738
C68: 220p C0G 50V; C_0805_2012Metric; MPN CC0805JRNPO0BN221; LCSC C113819
D1: SS310; D_SMA; MPN SS310; LCSC C15874
D2: SMBJ60A; D_SMB; MPN SMBJ60A; LCSC C49066953
F1: PTC 0.75A 60V; Fuse_1812_4532Metric; MPN 1812L075/60GR; LCSC C48985874
J1: 24V_INPUT; TerminalBlock_Phoenix_MKDS-1,5-3_1x03_P5.00mm_Horizontal; MPN WJ128V-5.0-3P; LCSC C8270
L1: 33u 2.2A; L_10.4x10.4_H4.8; MPN SMDRH104R-330MT; LCSC C9936
R55: 41.2k 1%; R_0805_2012Metric; MPN FRC0805F4122TS; LCSC C2933440
R56: 158k 1%; R_0805_2012Metric; MPN RT0805BRD07158KL; LCSC C865205
R57: 49.9k 1%; R_0805_2012Metric; MPN 0805W8F4992T5E; LCSC C17719
R58: 150k 1%; R_0805_2012Metric; MPN 0805W8F1503T5E; LCSC C17470
R59: 33.2k 1%; R_0805_2012Metric; MPN FRC0805F3322TS; LCSC C2933418
R60: 10k 1%; R_0805_2012Metric; MPN 0805W8F1002T5E; LCSC C17414
TP1: GND_CTRL; TestPoint_THTPad_D2.0mm_Drill1.0mm
TP2: +5V_CTRL; TestPoint_THTPad_D2.0mm_Drill1.0mm
U14: LM5164DDAR; SOIC-8-1EP_3.9x4.9mm_P1.27mm_EP2.41x3.3mm; MPN LM5164DDAR; LCSC C477928

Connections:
/+5V_CTRL: C55.1, C64.1, C65.1, C67.2, L1.2, R56.1, TP2.1 (Pin_1_1); also elsewhere on the board
/+24V_PROT: C53.1, C54.1, C63.1, D1.1 (K), D2.1 (K), R59.1, U14.2 (VIN); also elsewhere on the board
/CHASSIS_SHIELD: J1.3; also elsewhere on the board
/GND_CTRL: C53.2, C54.2, C55.2, C63.2, C64.2, C65.2, D2.2 (A), J1.2, R55.2, R57.2, R60.2, TP1.1 (Pin_1_1), U14.1 (GND), U14.9 (EP); also elsewhere on the board
/POWER/+24V_FUSED: D1.2 (A), F1.2
/POWER/+24V_RAW: F1.1, J1.1
/POWER/BST_5V: C62.1, U14.7 (BST)
/POWER/FB_5V: C68.2, R56.2, R57.1, U14.5 (FB)
/POWER/RIPPLE_INJ: C67.1, C68.1, R58.2
/POWER/RON_SET: R55.1, U14.4 (RON)
/POWER/SW_5V: C62.2, L1.1, R58.1, U14.8 (SW)
/POWER/VIN_UVLO: R59.2, R60.1, U14.3 (EN/UVLO)
